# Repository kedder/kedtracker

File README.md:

# Ked Tracker - Open Glider Network tracker hardware

Based on design by glidernet.org project: http://wiki.glidernet.org/ogn-tracker-diy.

It is a small airborn avionic device that periodically transmits aircraft
position. Signal is picked up by ground-based receivers and published on Open
Glider Network, so that aircraft position can be found on  various aircraft
tracking systems, like http://glidertracker.de/ or
https://www.flightradar24.com/. It is also received by other OGN tracker
devices in the vicinity and can be used to improve pilot' situation awareness.
See http://wiki.glidernet.org/ for more information.

Ked Tracker is designed using [KiCad](http://kicad-pcb.org/) electronic schematic and PCB design software.

## Features

* Can be powered from onboard 12V power supply (or any 9-24V power
  supply for that matter).

* Standard NMEA output.

* Uses FLARM NMEA sentences to report detected nearby aircrafts for
  interoperability with existing hardware and software.

* Communication via standard IGC RJ45 socket.
  Allows to re-use existing equipment like FLARM viewers or cables.

* Communication via USB interface. Device is visible as virtual COM port
  when connected to a computer. Requires no special cables other then standerd
  micro-USB cable. Device can also be powered by 5V from USB interface.

* Communication via Bluetooth. For hassle-free wireless connection with
  phone or tablet.

* Barometric sensor onboard for more precise altitude measurement.

* Slot for SD-card. Currently for logging device activity. Firmware for IGC
  flight logger is pending.

* Beeper to provide sound feedback for important events.

## Schematics

Current schematics can be also downloaded in
[PDF format](hardware/render/kedtracker.pdf?raw=true).

## Setting Up Development Environment

You will need to install additional packages for development. Packages for
ubuntu are specified here; other operating systems might have similar
requirements.

### Building Firmware and Flashing MCU

```
sudo apt install gcc-arm-none-eabi openocd picocom
sudo add-user `whoami` plugdev
sudo add-user `whoami` dialout
```

### Developing Hardware

```
sudo apt install kicad
```

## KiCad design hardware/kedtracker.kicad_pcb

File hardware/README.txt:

OGN Tracker Hardware

Notes:

To create laser printer templates plot:

  Front Layer: Mirrored
  Bottom Layer: Non-mirrored

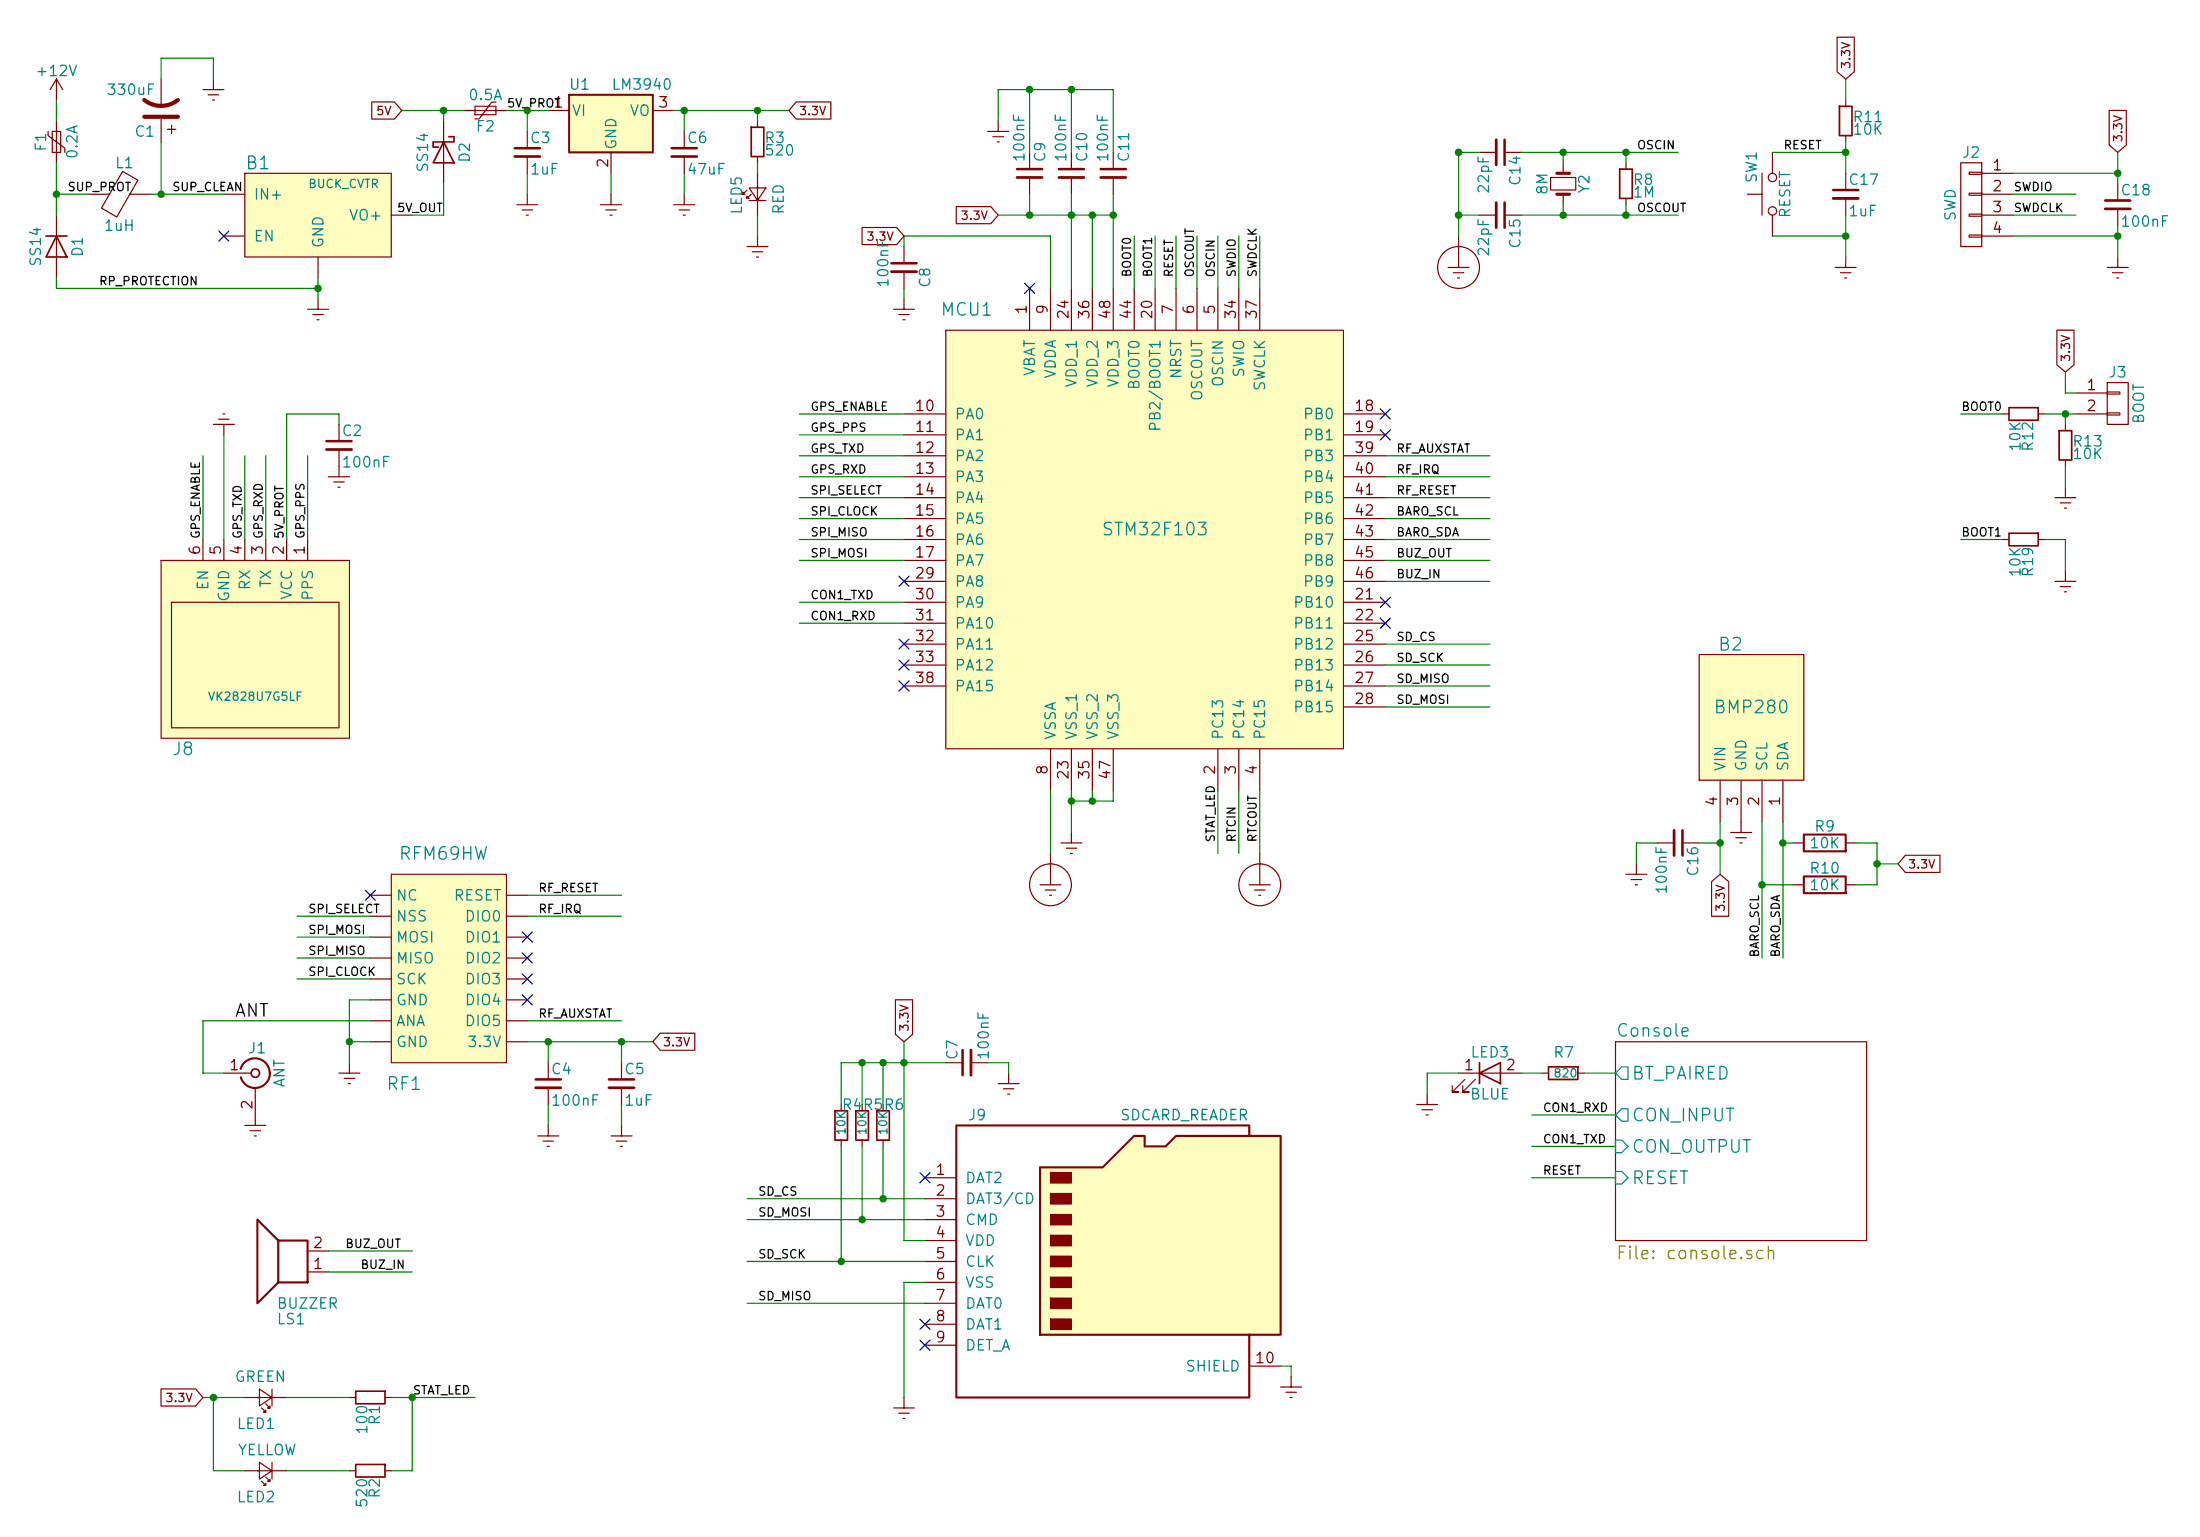
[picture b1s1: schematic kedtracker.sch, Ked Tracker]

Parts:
B1: BUCK_CVTR; Buck_Converter_Sm
B2: BMP280
C1: 330uF; CP_Radial_D6.3mm_P2.50mm
C2, C4, C7, C8, C9, C10, C11, C16, C18: 100nF; C_0805
C3, C5, C17: 1uF; C_1206
C6: 47uF; C_1210
C14, C15: 22pF; C_0603
D1, D2: SS14; D_SMA_Standard
F1: 0.2A; Fuse_SMD1206_Reflow
F2: 0.5A; Fuse_SMD1206_Reflow
J1: ANT; SMA_CONN
J2: SWD; Pin_Header_Straight_1x04_Pitch2.54mm
J3: BOOT; Pin_Header_Straight_2x01_Pitch2.54mm
J8: VK2828U7G5LF; Molex_PicoBlade_53047-0610_06x1.25mm_Straight
J9: SDCARD_READER; SDCARD_BOMB
L1: 1uH; INDUCTOR_V
LED1: GREEN; LED_D5.0mm_Horizontal_O3.81mm_Z3.0mm
LED2: YELLOW; LED_0603
LED3: BLUE; LED_D5.0mm_Horizontal_O3.81mm_Z3.0mm
LED5: RED; LED_0603
LS1: BUZZER; Buzzer_12x9.5RM7.6
MCU1: STM32F103; LQFP-48_7x7mm_Pitch0.5mm
R1: 100; R_0805
R2, R3: 520; R_0805
R4, R5, R6, R9, R10, R11, R12, R13, R19: 10K; R_0805
R7: 820; R_0805
R8: 1M; R_0805
RF1: RFM69HW
SW1: RESET; SW_SPST_SKQG
U1: LM3940; SOT-223-3Lead_TabPin2
Y2: 8M; Crystal_SMD_HC49-SD

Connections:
3.3V: B2.4 (VIN), C4.1, C5.1, C6.1, C7.1, C8.1, C9.2, C10.2, C11.2, C16.1, C18.1, J2.1, J3.1, J9.4 (VDD), LED1.2 (A), LED2.2 (A), MCU1.9 (VDDA), MCU1.24 (VDD_1), MCU1.36 (VDD_2), MCU1.48 (VDD_3), R3.1, R4.1, R5.1, R6.1, R9.2, R10.2, R11.1, RF1.1 (3.3V), U1.3 (VO); also elsewhere on the board
5V: D2.1 (K), F2.1; also elsewhere on the board
+12V: F1.1; also elsewhere on the board
/5V_OUT: B1.4 (VO+), D2.2 (A)
/5V_PROT: C2.1, C3.1, F2.2, J8.2 (VCC), U1.1 (VI)
/ANT: J1.1 (In), RF1.10 (ANA)
/BARO_SCL: B2.2 (SCL), MCU1.42 (PB6), R10.1
/BARO_SDA: B2.1 (SDA), MCU1.43 (PB7), R9.1
/BOOT0: MCU1.44 (BOOT0), R12.2
/BOOT1: MCU1.20 (PB2/BOOT1), R19.2
/BUZ_IN: LS1.1, MCU1.46 (PB9)
/BUZ_OUT: LS1.2, MCU1.45 (PB8)
/CON1_RXD: MCU1.31 (PA10); also elsewhere on the board
/CON1_TXD: MCU1.30 (PA9); also elsewhere on the board
/Console/BT_PAIRED: R7.1; also elsewhere on the board
/GPS_ENABLE: J8.6 (EN), MCU1.10 (PA0)
/GPS_PPS: J8.1 (PPS), MCU1.11 (PA1)
/GPS_RXD: J8.3 (TX), MCU1.13 (PA3)
/GPS_TXD: J8.4 (RX), MCU1.12 (PA2)
/OSCIN: C14.1, MCU1.5 (OSCIN), R8.1, Y2.1
/OSCOUT: C15.1, MCU1.6 (OSCOUT), R8.2, Y2.2
/RESET: C17.1, MCU1.7 (NRST), R11.2, SW1.2; also elsewhere on the board
/RF_AUXSTAT: MCU1.39 (PB3), RF1.2 (DIO5)
/RF_IRQ: MCU1.40 (PB4), RF1.7 (DIO0)
/RF_RESET: MCU1.41 (PB5), RF1.8 (RESET)
/SD_CS: J9.2 (DAT3/CD), MCU1.25 (PB12), R6.2
/SD_MISO: J9.7 (DAT0), MCU1.27 (PB14)
/SD_MOSI: J9.3 (CMD), MCU1.28 (PB15), R5.2
/SD_SCK: J9.5 (CLK), MCU1.26 (PB13), R4.2
/SPI_CLOCK: MCU1.15 (PA5), RF1.12 (SCK)
/SPI_MISO: MCU1.16 (PA6), RF1.13 (MISO)
/SPI_MOSI: MCU1.17 (PA7), RF1.14 (MOSI)
/SPI_SELECT: MCU1.14 (PA4), RF1.15 (NSS)
/STAT_LED: MCU1.2 (PC13), R1.1, R2.1
/SUP_CLEAN: B1.2 (IN+), C1.1, L1.1
/SUP_PROT: D1.1 (K), F1.2, L1.2
/SWDCLK: J2.3, MCU1.37 (SWCLK)
/SWDIO: J2.2, MCU1.34 (SWIO)
Earth: B1.3 (GND), B2.3 (GND), C1.2, C2.2, C3.2, C4.2, C5.2, C6.2, C7.2, C8.2, C9.1, C10.1, C11.1, C16.2, C17.2, C18.2, D1.2 (A), J1.2 (Ext), J2.4, J8.5 (GND), J9.6 (VSS), J9.10 (SHIELD), LED3.1 (K), LED5.1 (K), MCU1.23 (VSS_1), MCU1.35 (VSS_2), MCU1.47 (VSS_3), R13.2, R19.1, RF1.9 (GND), RF1.11 (GND), SW1.1, U1.2 (GND); also elsewhere on the board
Earth_Protective: C14.2, C15.2, MCU1.4 (PC15), MCU1.8 (VSSA)
unnamed: J3.2, R12.1, R13.1
unnamed: LED1.1 (K), R1.2
unnamed: LED2.1 (K), R2.2
unnamed: LED3.2 (A), R7.2
unnamed: LED5.2 (A), R3.2

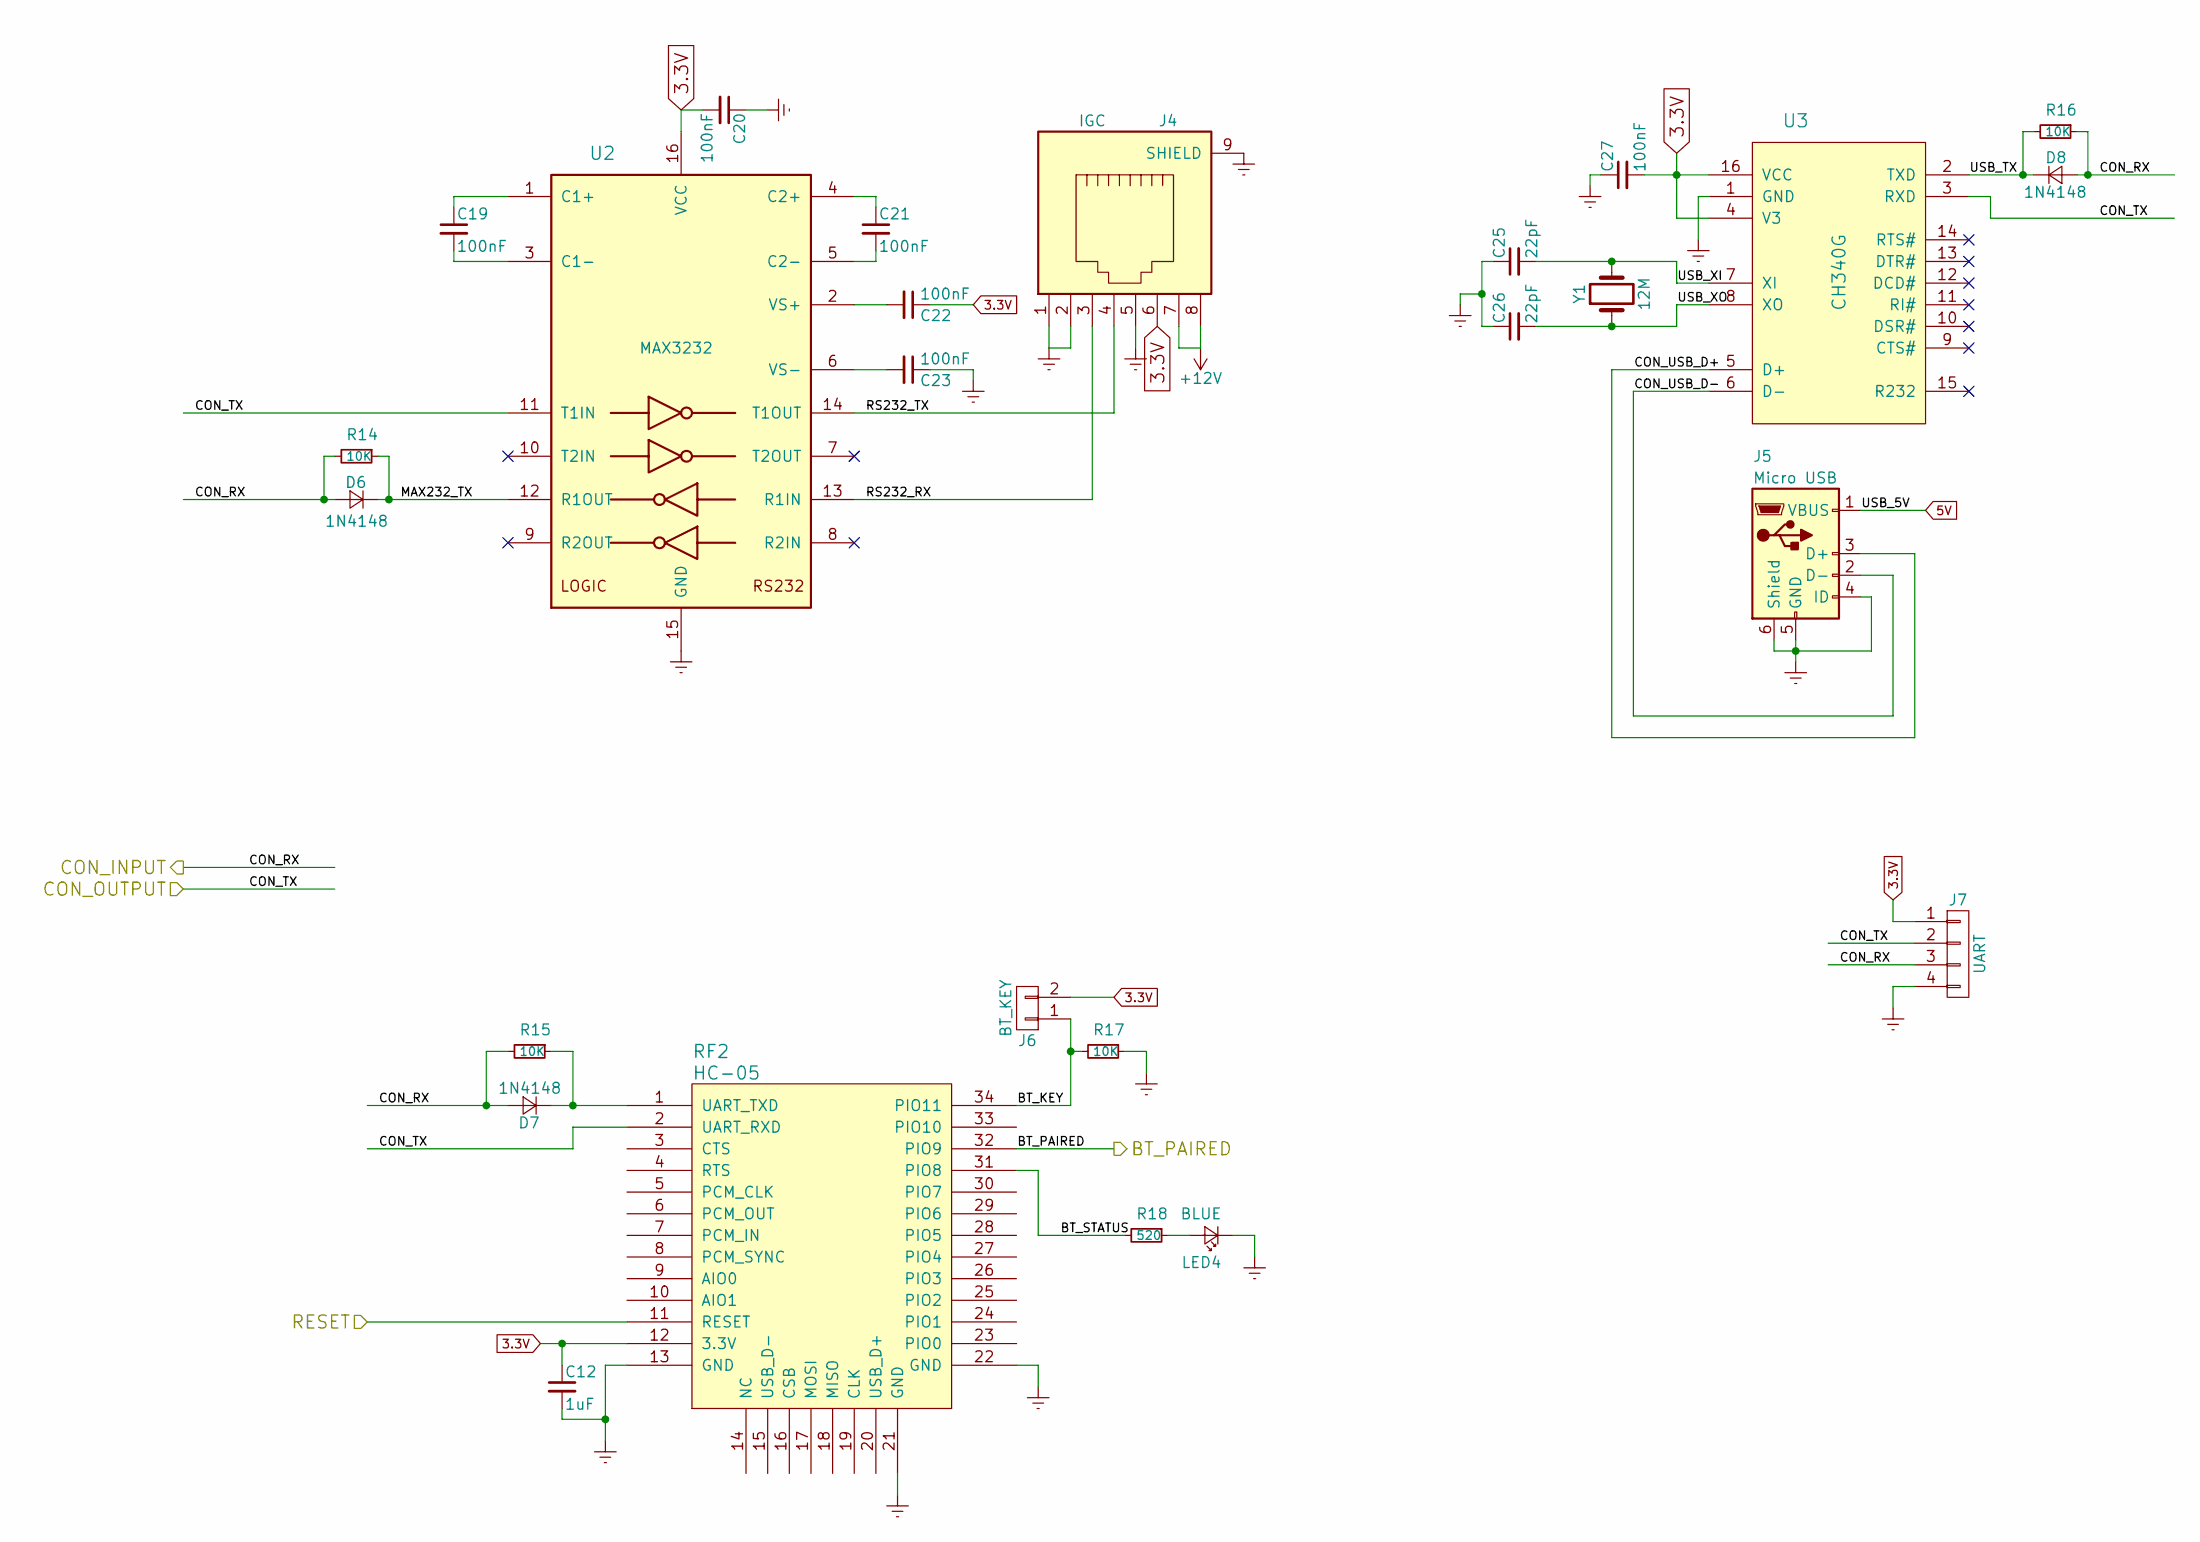
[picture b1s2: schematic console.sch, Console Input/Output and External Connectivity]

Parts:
C12: 1uF; C_1206
C19, C20, C21, C22, C23, C27: 100nF; C_0805
C25, C26: 22pF; C_0603
D6, D7, D8: 1N4148; D_1206
J4: IGC; RJ45_SOCKET_SHLD
J5: Micro USB; USB_Micro
J6: BT_KEY; Pin_Header_Straight_2x01_Pitch2.54mm
J7: UART; Pin_Header_Straight_1x04_Pitch2.54mm
LED4: BLUE; LED_0603
R14, R15, R16, R17: 10K; R_0805
R18: 520; R_0805
RF2: HC-05
U2: MAX3232; SOIC-16_3.9x9.9mm_Pitch1.27mm
U3: CH340G; SOIC-16_3.9x9.9mm_Pitch1.27mm
Y1: 12M; Crystal_HC49-4H_Vertical

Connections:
3.3V: C12.1, C20.2, C22.1, C27.2, J4.6, J6.2, J7.1, RF2.12 (3.3V), U2.16 (VCC), U3.4 (V3), U3.16 (VCC); also elsewhere on the board
5V: J5.1 (VBUS); also elsewhere on the board
+12V: J4.7, J4.8; also elsewhere on the board
/CON1_RXD: D6.2 (A), D7.2 (A), D8.2 (A), J7.3, R14.2, R15.2, R16.1; also elsewhere on the board
/CON1_TXD: J7.2, RF2.2 (UART_RXD), U2.11 (T1IN), U3.3 (RXD); also elsewhere on the board
/Console/BT_KEY: J6.1, R17.2, RF2.34 (PIO11)
/Console/BT_PAIRED: RF2.32 (PIO9); also elsewhere on the board
/Console/BT_STATUS: R18.2, RF2.31 (PIO8)
/Console/CON_USB_D+: J5.3 (D+), U3.5 (D+)
/Console/CON_USB_D-: J5.2 (D-), U3.6 (D-)
/Console/MAX232_TX: D6.1 (K), R14.1, U2.12 (R1OUT)
/Console/RS232_RX: J4.3, U2.13 (R1IN)
/Console/RS232_TX: J4.4, U2.14 (T1OUT)
/Console/USB_TX: D8.1 (K), R16.2, U3.2 (TXD)
/Console/USB_XI: C25.2, U3.7 (XI), Y1.2
/Console/USB_XO: C26.2, U3.8 (XO), Y1.1
/RESET: RF2.11 (RESET); also elsewhere on the board
Earth: C12.2, C20.1, C23.1, C25.1, C26.1, C27.1, J4.1, J4.2, J4.5, J4.9 (SHIELD), J5.4 (ID), J5.5 (GND), J5.6 (Shield), J7.4, LED4.1 (K), R17.1, RF2.13 (GND), RF2.21 (GND), RF2.22 (GND), U2.15 (GND), U3.1 (GND); also elsewhere on the board
unnamed: C19.1, U2.1 (C1+)
unnamed: C19.2, U2.3 (C1-)
unnamed: C21.1, U2.4 (C2+)
unnamed: C21.2, U2.5 (C2-)
unnamed: C22.2, U2.2 (VS+)
unnamed: C23.2, U2.6 (VS-)
unnamed: D7.1 (K), R15.1, RF2.1 (UART_TXD)
unnamed: LED4.2 (A), R18.1

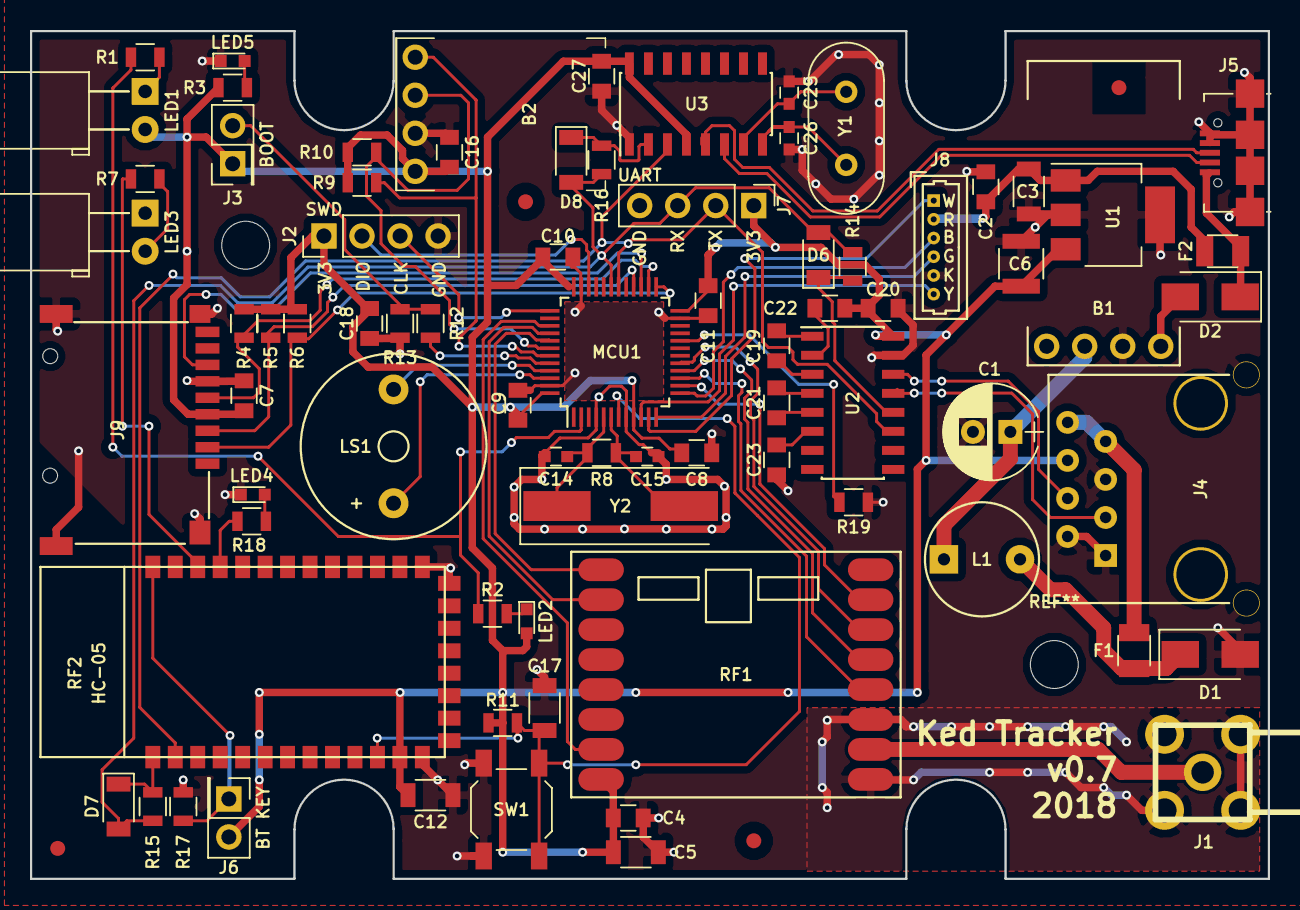
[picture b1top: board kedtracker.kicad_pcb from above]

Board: 2 copper layers, 82.7 x 56.6 mm, 78 parts (0 on the bottom side), 63 nets.

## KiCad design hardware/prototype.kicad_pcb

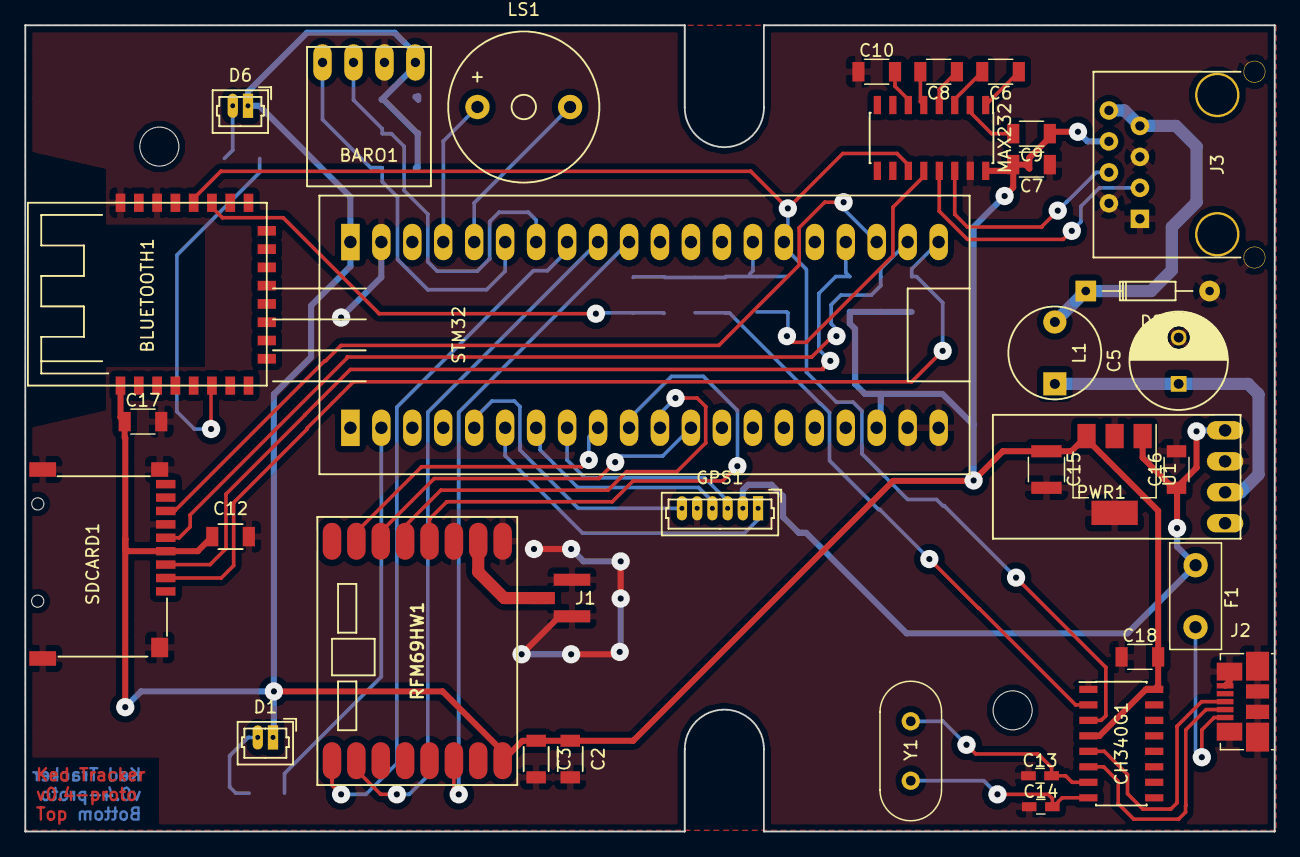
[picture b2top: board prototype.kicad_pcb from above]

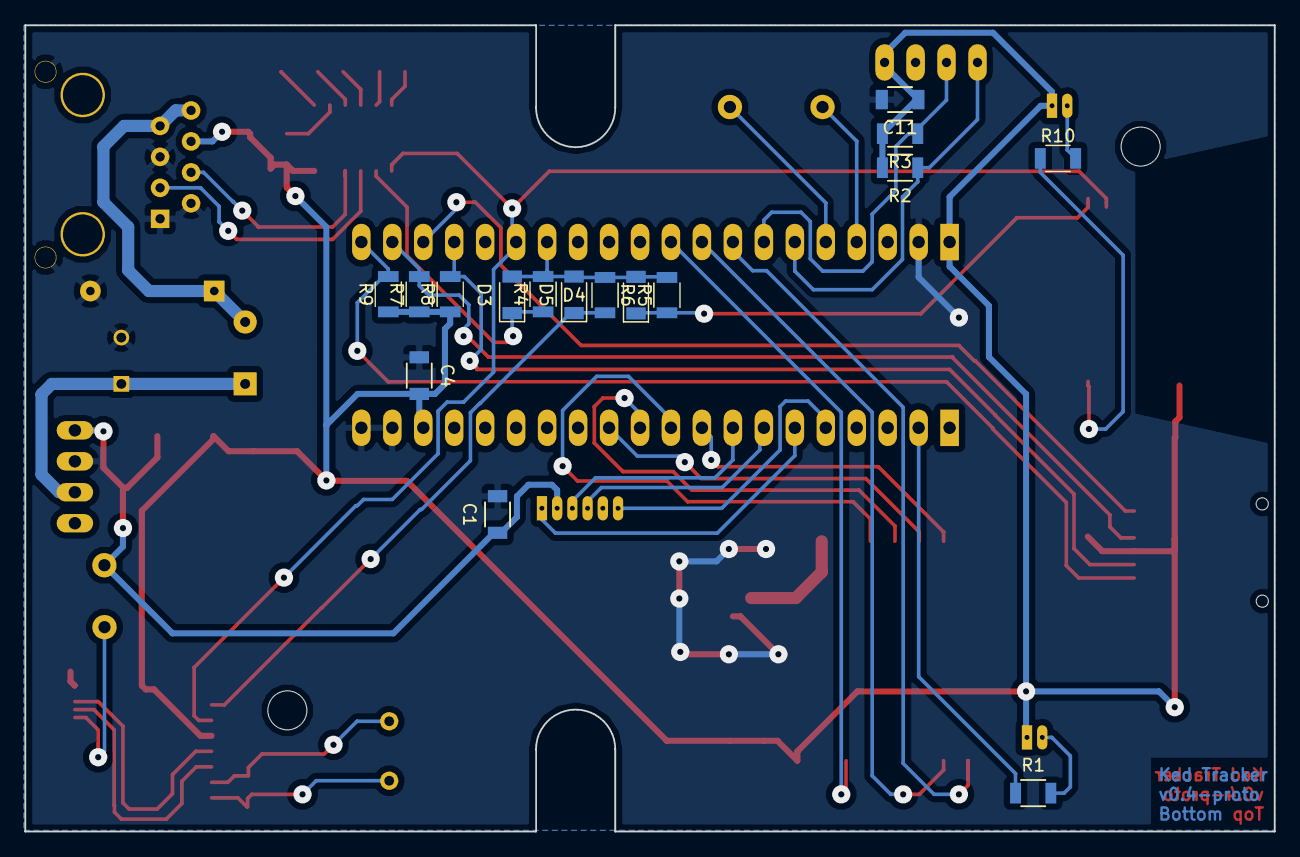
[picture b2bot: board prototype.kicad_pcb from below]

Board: 2 copper layers, 102.5 x 66.1 mm, 51 parts (16 on the bottom side), 47 nets.

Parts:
BARO1: BMP280; BMP280_HandSoldering
BLUETOOTH1: JDY-08
C1, C3, C6, C7, C8, C9, C10, C11, C12, C17, C18: 100nF; C_1206
C2, C4, C16: 1uF; C_1206
C5: 330uF; C_Radial_D8_L13_P3.8
C13, C14: 22pF; C_0603_HandSoldering
C15: 47uF; C_1210
CH340G1: CH340G; SOIC-16_3.9x9.9mm_Pitch1.27mm
D1: LED_STAT; Molex_PicoBlade_02x1.25mm_HandSoldering
D2: 1N4001; Diode_DO-35_SOD27_Horizontal_RM10
D3, D4, D5: 1N4148; D_1206
D6: LED_BT; Molex_PicoBlade_02x1.25mm_HandSoldering
F1: 1A; Fuse_TE5_Littlefuse-395Series
GPS1: VK2828U7G5LF; Molex_PicoBlade_06x1.25mm_HandSoldering
J1: ANT; IPEX
J2: Micro USB; USB_Micro-B_Molex_47346-0001
J3: IGC; RJ45_SOCKET_SHLD
L1: 1uH; INDUCTOR_V
LS1: Buzzer; Buzzer_12x9.5RM7.6
MAX232: MAX3232; SOIC-16_3.9x9.9mm_Pitch1.27mm
PWR1: BUCK_CVTR; Buck_Converter_Sm_HandSoldering
R1, R10: 82; R_1206
R2, R3, R4, R5, R6, R7, R8, R9: 10K; R_1206
RFM69HW1: RFM69HW
SDCARD1: Micro SD Reader; SDCARD_BOMB
STM32: STM32DEVBOARD; STM32DEVBOARD_HandSoldering
U1: LM2936-3.3; SOT-223-3Lead_TabPin2
Y1: 12M; Crystal_HC49-4H_Vertical

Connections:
3.3V: BARO1.1, BLUETOOTH1.1, C2.1, C3.1, C4.2, C7.2, C9.1, C11.1, C12.1, C15.1, C17.1, C18.2, CH340G1.4, CH340G1.16, D1.1, D6.1, J3.6, MAX232.16, R2.2, R3.2, R7.1, R8.1, R9.1, RFM69HW1.1, SDCARD1.4, STM32.18, U1.3
5V: C1.1, C16.1, F1.1, GPS1.2, PWR1.4, U1.1
+12V: D2.1, J3.7, J3.8, L1.2
/ANT: J1.1, RFM69HW1.10
/AUX_STATUS: RFM69HW1.3, STM32.30
/BARO_SCL: BARO1.3, R3.1, STM32.27
/BARO_SDA: BARO1.4, R2.1, STM32.26
/BUZ_IN: LS1.1, STM32.24
/BUZ_OUT: LS1.2, STM32.25
/CHIP_RESET: RFM69HW1.8, STM32.28
/CON1_RXD: D3.2, D4.2, D5.2, R4.2, R5.2, R6.1, STM32.34
/CON1_TXD: BLUETOOTH1.20, CH340G1.3, MAX232.11, STM32.35
/Console/BT_STATUS: BLUETOOTH1.6, R10.1
/Console/BT_TX: BLUETOOTH1.19, D4.1, R5.1
/Console/MAX232_TX: D3.1, MAX232.12, R4.1
/Console/RS232_RX: J3.3, MAX232.13
/Console/RS232_TX: J3.4, MAX232.14
/Console/USB_5V: F1.2, J2.1
/Console/USB_D+: CH340G1.5, J2.3
/Console/USB_D-: CH340G1.6, J2.2
/Console/USB_TX: CH340G1.2, D5.1, R6.2
/Console/USB_XI: C13.2, CH340G1.7, Y1.2
/Console/USB_XO: C14.2, CH340G1.8, Y1.1
/GPS_ENABLE: GPS1.6, STM32.5
/GPS_PPS: GPS1.1, STM32.6
/GPS_RXD: GPS1.3, STM32.8
/GPS_TXD: GPS1.4, STM32.7
/INT_REQ: RFM69HW1.7, STM32.29
/LED: R1.1, STM32.2
/SD_CS: R9.2, SDCARD1.2, STM32.40
/SD_MISO: SDCARD1.7, STM32.38
/SD_MOSI: R8.2, SDCARD1.3, STM32.37
/SD_SCK: R7.2, SDCARD1.5, STM32.39
/SPI_CLOCK: RFM69HW1.12, STM32.10
/SPI_MISO: RFM69HW1.13, STM32.11
/SPI_MOSI: RFM69HW1.14, STM32.12
/SPI_SELECT: RFM69HW1.15, STM32.9
/SUP_CLEAN: C5.1, L1.1, PWR1.2
Earth: BARO1.2, BLUETOOTH1.22, BLUETOOTH1.24, C1.2, C2.2, C3.2, C4.1, C5.2, C7.1, C10.1, C11.2, C12.2, C13.1, C14.1, C15.2, C16.2, C17.2, C18.1, CH340G1.1, D2.2, GPS1.5, J1.2, J2.5, J2.6, J3.1, J3.2, J3.5, J3.9, MAX232.15, PWR1.3, RFM69HW1.9, RFM69HW1.11, SDCARD1.6, SDCARD1.10, STM32.19, U1.2
unnamed: C6.1, MAX232.1
unnamed: C6.2, MAX232.3
unnamed: C8.1, MAX232.4
unnamed: C8.2, MAX232.5
unnamed: C9.2, MAX232.2
unnamed: C10.2, MAX232.6
unnamed: D1.2, R1.2
unnamed: D6.2, R10.2

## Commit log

2017-08-23 Initial commit
    Allow to flash microcontroller using openocd
2017-08-23 Hardware project added
2017-08-23 Make dev environment
2017-08-23 Add firmware as submodule
2017-08-23 Add module docs
2017-08-27 Improvements to make hand-made board easier to produce
    * Wider copper base for pins
    * Proper size of CPU board
    * Added console headers
2017-08-27 Larger vias and tracks for DIY production
2017-08-27 Version 0.2.0, manufactured
2017-08-29 Allow on-board GDB debugging
2017-08-31 Design of box label finalized
2017-09-01 MAX232 added and 2 RJ45 sockets for comms
2017-09-16 Hardware 0.3 released for manufacturing
2017-09-16 Added docs for used components
2017-09-16 Show Hardware Schematics
2017-09-16 More complete README
2017-11-04 Support starting st-link debugger daemon
2017-11-04 Label template for 0.3 release
2017-11-04 Gerbers for 0.3 hardware release
2017-11-04 Configuration for bluetooth documented
2017-11-05 Various updates to schematics and experiments with layout for new box
2017-11-12 Routed prototype board for HAMMOND 1593N box
2017-11-12 Datasheets for new components
2017-11-25 Configuration notes
2017-11-25 STM32 dev-board based schematics
2017-11-25 Document some configuration options
2017-11-25 Unfinished pcb layouts
2017-11-25 Basic scaffolding for the GUI tool
2017-12-03 Unverified attempt on standalone STM32 chip
2017-12-09 Correct status diode direction
2017-12-09 Schematics pdf updated
2017-12-11 Remove obsolete doc
2017-12-11 Add HC-05 bluetooth symbol
2017-12-11 Label for 3rd device
2017-12-11 Simple drawings for box panels
2017-12-11 All the used footprints moved to project directory
2017-12-14 v0.6 routed
2017-12-16 Labels and slight tweaks for 0.6
2017-12-16 Components renamed to be more uniform
2017-12-17 More tweaks for new box
2017-12-17 Add symbox for lib file
2017-12-17 Label for new box
2017-12-17 Naming library properly
2017-12-17 Updating schematics for publishing
2017-12-17 Updated schematics and README
2017-12-17 More tweaks before release
2017-12-18 Final tweaks
2017-12-18 HW version 0.6 released for manufacturing
2017-12-18 Remove non-archived gerbers (added by accident)
2018-01-13 Record what needs to be done with HC-05 BT module
2018-01-13 Better placement for values on Fab layers
2018-01-13 Upgrade firmware to the latest upstream version
2018-01-23 Sideplates and GPS support for Hammond 1593L enclosure
2018-02-03 Prepare fabrication layer for assembly
    * Proper placement of labels on F.Fab layer
    * Element outlines
    * Correct values of used components
    * LED values indicate color, rather then function
2018-02-03 Ignore tmp directory
2018-02-04 Changes and fixes for 0.7
    * Different 4-pin reset button (because I have a lot of those)
    * Bluethooth "paired" and "status" leds swapped - dashboard
    led will show "paired" status and will not annoyingly blink all
    the time
2018-02-04 Baro board turned 90 degrees to fit into the board
2018-02-14 Updates for power supply and reset button
2018-02-16 Target to flash setup firmware
2018-02-16 Reset button resets bluetooth chip as well
2018-02-18 Preparing release 0.7
2018-02-19 Correct capacitor size
2018-02-24 Document packages required for development
2018-02-24 Schematics updated to 0.7
2018-02-24 Gerbers for 0.7 accepted for manufacturing
2018-02-26 Ignore VS Code files
2018-02-26 Document required user groups for flashing and console
2018-03-01 Script to configure and check the hardware
2018-03-01 Ignore python virtualenv
2018-03-04 make target for automatic deploy script
2018-03-04 Unbreak gps frame model
2018-03-04 Box models for 0.6 and 0.7
2018-03-04 More robust virtualenv creation
2018-03-06 flash-usb target
2018-03-07 Boxes for 0.6 and 0.7 ready for mass production
2018-03-07 Label generator and labels for recent versions
2018-03-11 Thinner plates to accomodate the thickness of labels
2018-03-18 Bootloader - initial version
2018-03-18 Add package target to produce firmware update file
2018-03-18 Limit size of bootloader to 7K
    Application will load from 0x08002000.
2018-03-18 Add licence - GPL-3
2018-03-18 Bootloader-based firmware
2018-03-18 Correct TX power configuration note
2018-03-19 Less verbose building
2018-03-19 Compile to the right memory section
2018-03-19 Close files in the same function that opens them
2018-03-19 Configurable bootloader version and name
2018-03-19 Flash both bootloader and main firmware
2018-03-19 Do not erase main firmware settings on upgrade
2018-03-20 Better alignment for FirmwareHeader data structure
2018-03-20 Report when no SD card is detected by bootloader
2018-03-20 Flash setup with bootloader
2018-03-20 New more generic deployment script
    More automated, controls the whole deployment process.
2018-03-21 New setup firmware (without watchdog)
2018-03-22 Simple manual page added
2018-03-23 Add serial number
2018-03-25 New firmware version
    - More robust SD card interface
    - Save parameters to Flash after reading from SDCard
2019-04-03 Support 64K smt chips
2019-04-03 Proper indent
2019-12-02 Detect flash size of the chip
2019-12-02 Specify addresses explicitly until binutils-arm-none-eabi-2.33
2019-12-02 Use modern way to create virtualenv
2019-12-02 Drop the "tool"
2019-12-02 Update schematics to latest KiCAD version
